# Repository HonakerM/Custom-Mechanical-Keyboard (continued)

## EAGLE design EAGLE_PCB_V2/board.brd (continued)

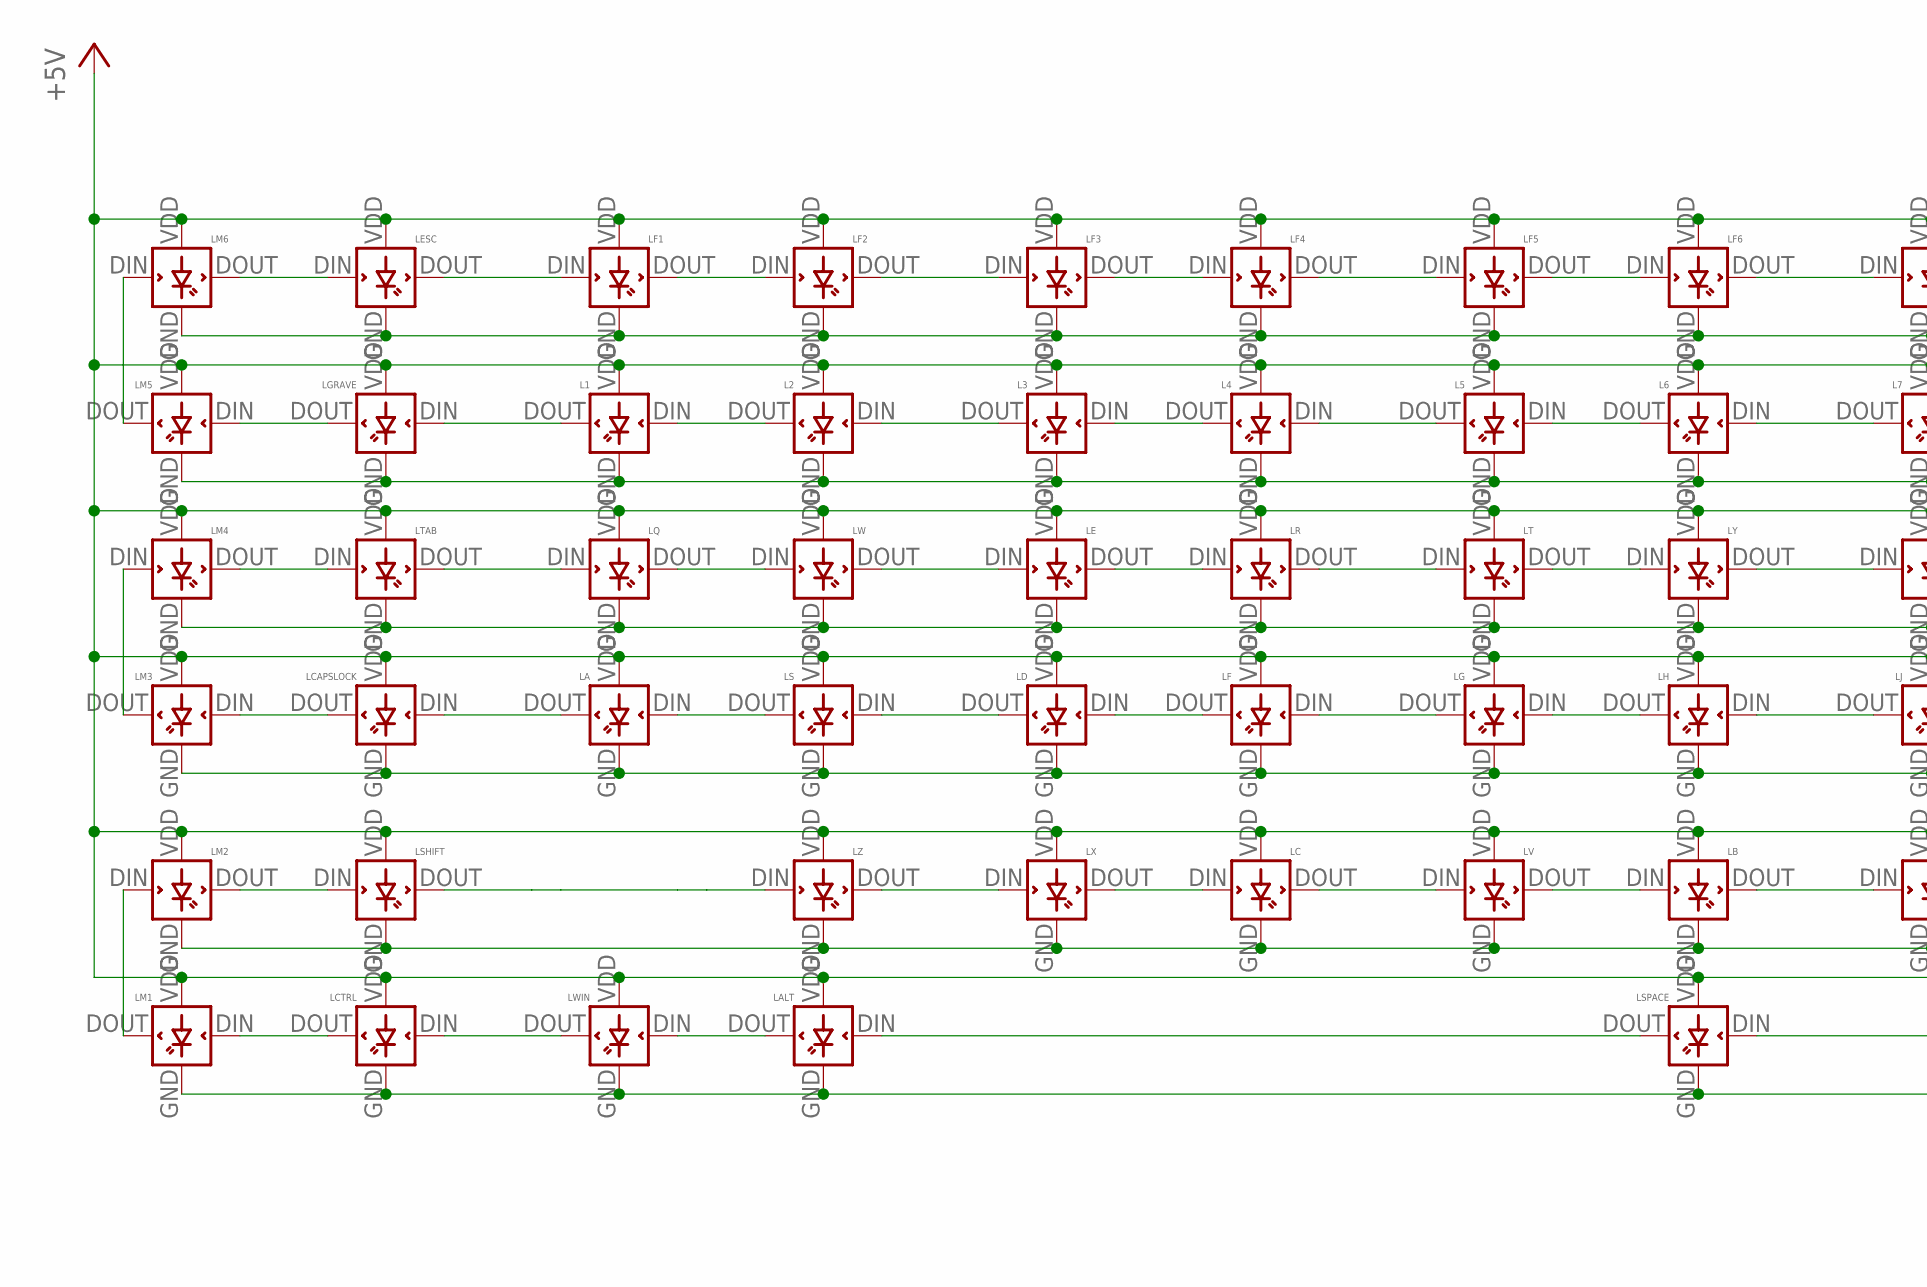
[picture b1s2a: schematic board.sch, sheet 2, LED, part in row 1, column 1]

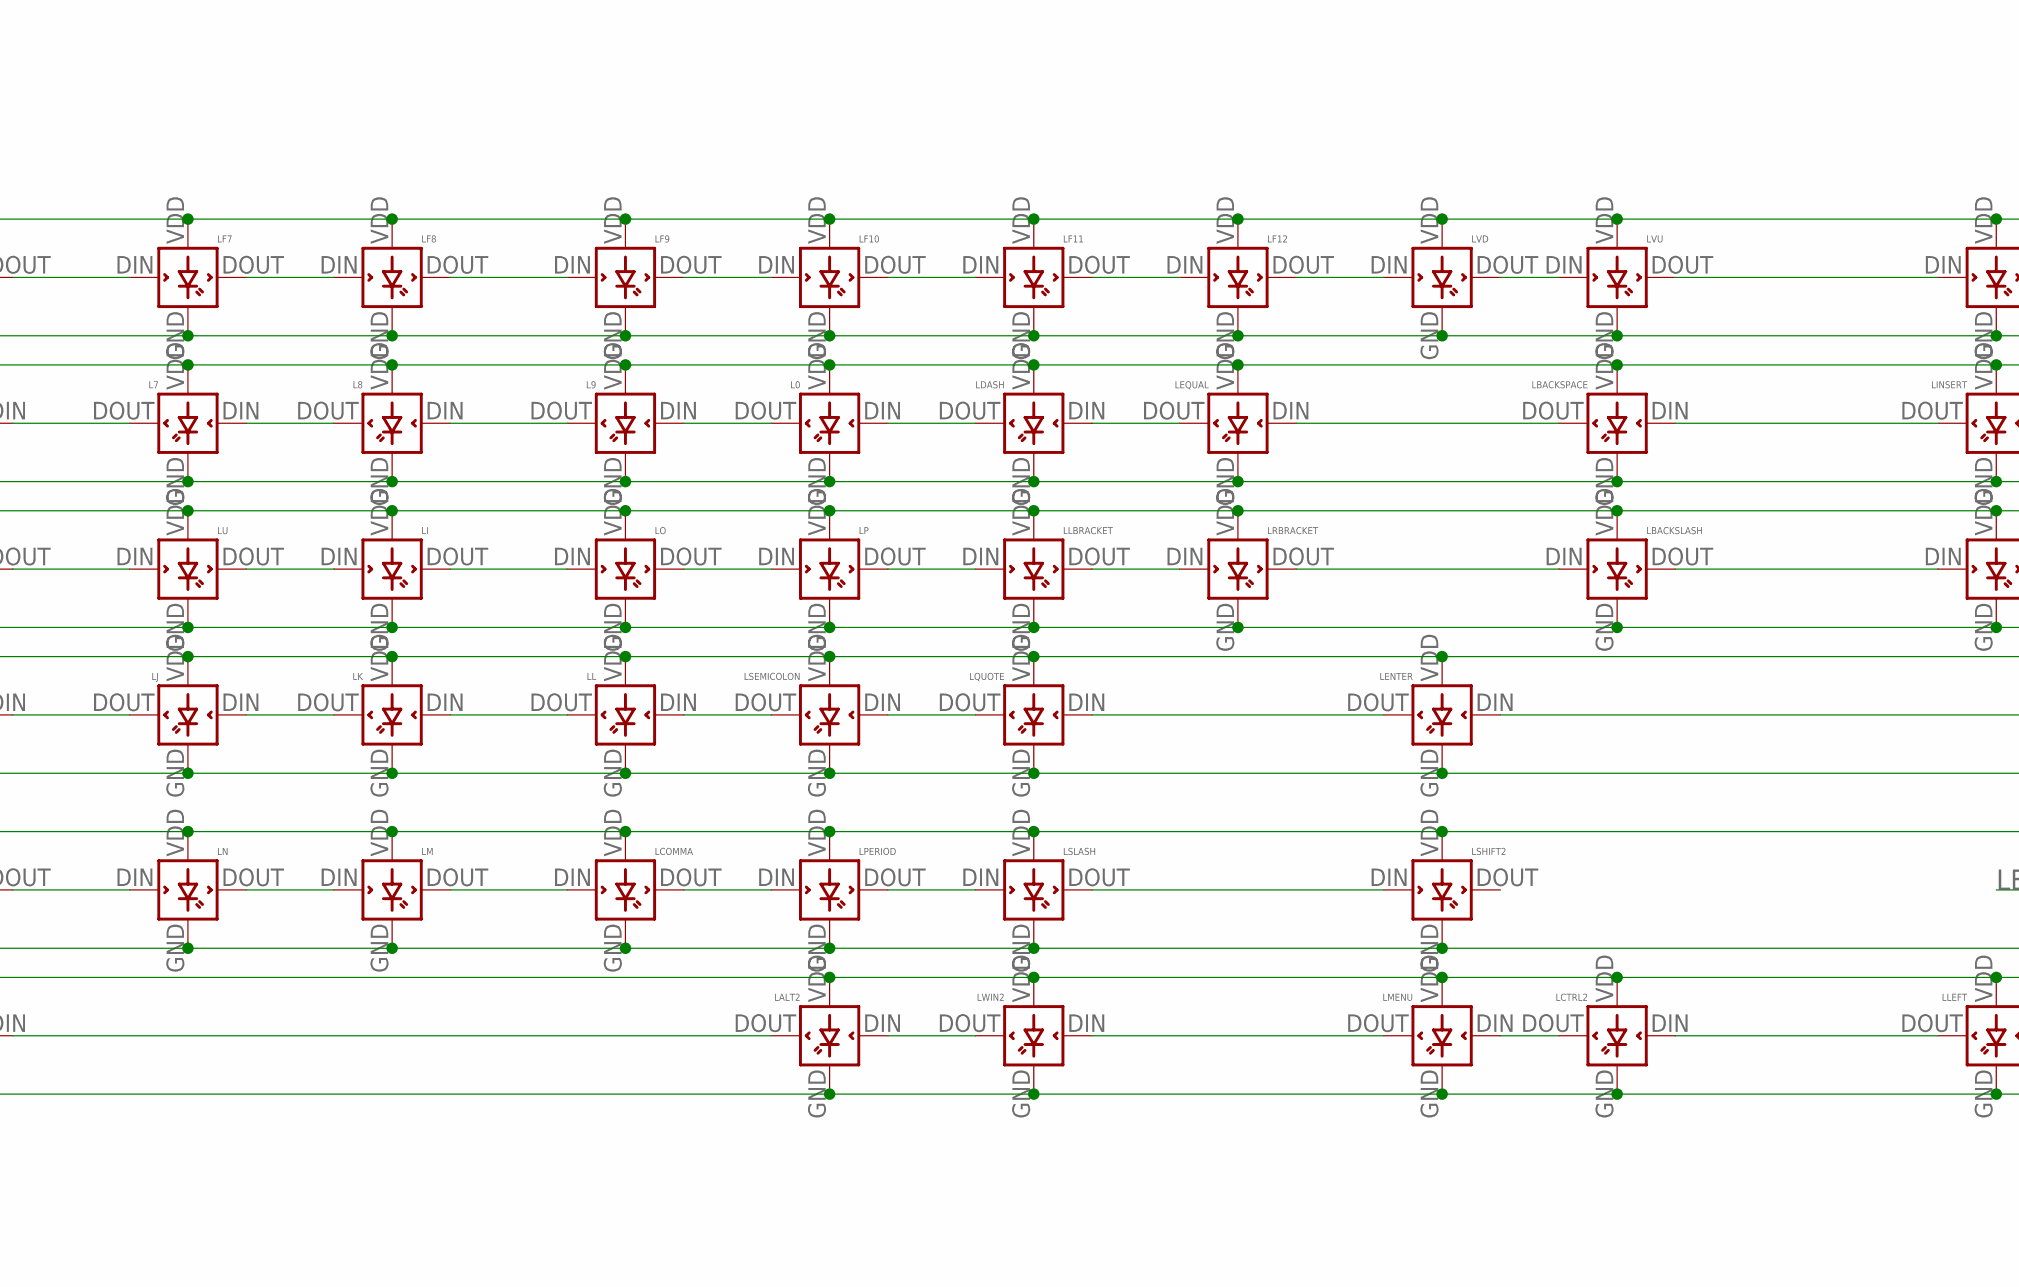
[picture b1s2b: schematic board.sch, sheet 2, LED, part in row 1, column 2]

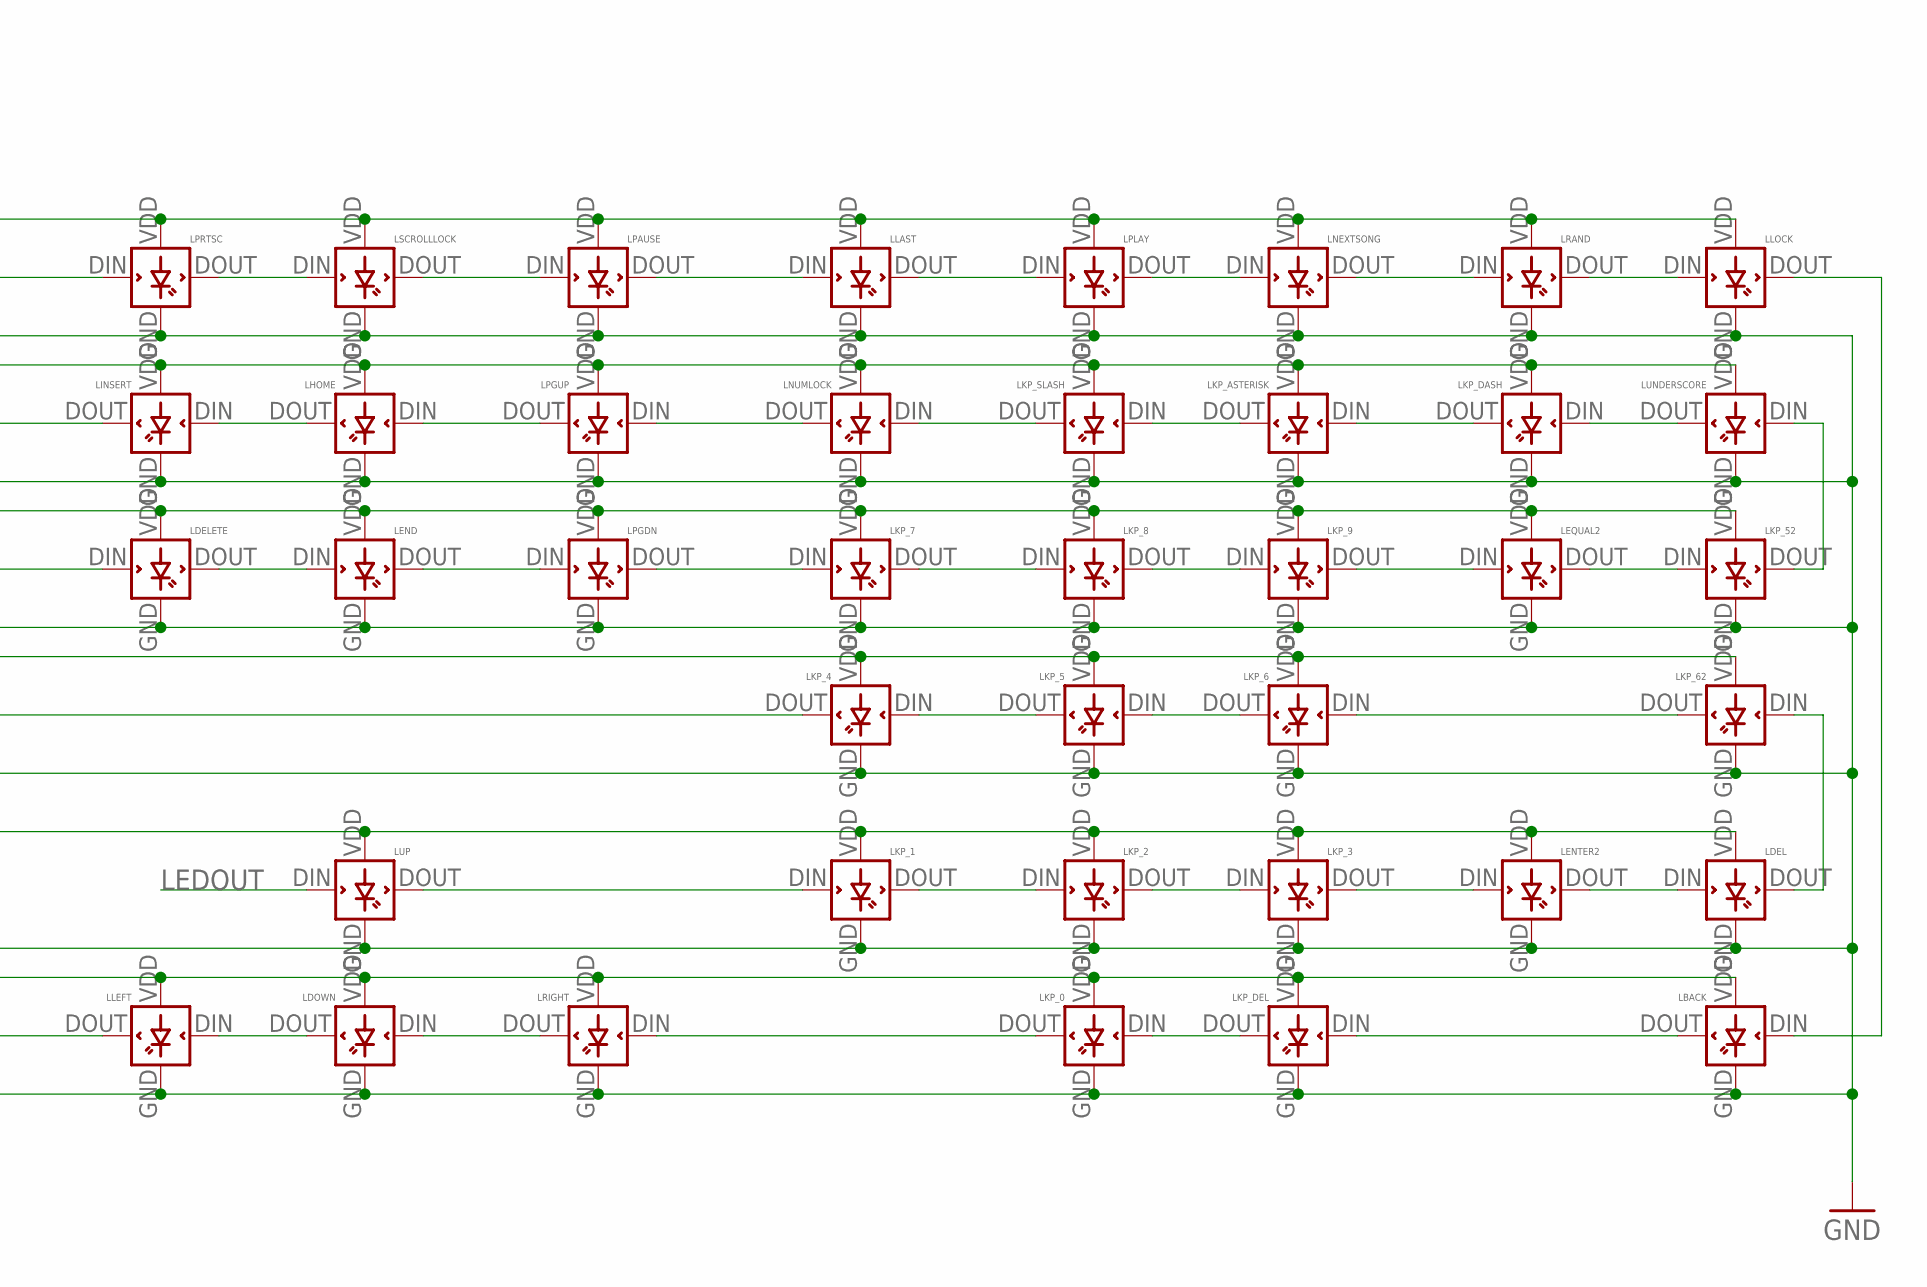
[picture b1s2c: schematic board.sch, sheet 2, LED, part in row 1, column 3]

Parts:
L0, L1, L2, L3, L4, L5, L6, L7, L8, L9: WS2812B-MINI
LA: WS2812B-MINI
LALT, LALT2: WS2812B-MINI
LB: WS2812B-MINI
LBACK: WS2812B-MINI
LBACKSLASH: WS2812B-MINI
LBACKSPACE: WS2812B-MINI
LC: WS2812B-MINI
LCAPSLOCK: WS2812B-MINI
LCOMMA: WS2812B-MINI
LCTRL, LCTRL2: WS2812B-MINI
LD: WS2812B-MINI
LDASH: WS2812B-MINI
LDEL: WS2812B-MINI
LDELETE: WS2812B-MINI
LDOWN: WS2812B-MINI
LE: WS2812B-MINI
LEND: WS2812B-MINI
LENTER, LENTER2: WS2812B-MINI
LEQUAL, LEQUAL2: WS2812B-MINI
LESC: WS2812B-MINI
LF, LF1, LF2, LF3, LF4, LF5, LF6, LF7, LF8, LF9, LF10, LF11, LF12: WS2812B-MINI
LG: WS2812B-MINI
LGRAVE: WS2812B-MINI
LH: WS2812B-MINI
LHOME: WS2812B-MINI
LI: WS2812B-MINI
LINSERT: WS2812B-MINI
LJ: WS2812B-MINI
LK: WS2812B-MINI
LKP_0, LKP_1, LKP_2, LKP_3, LKP_4, LKP_5, LKP_6, LKP_7, LKP_8, LKP_9, LKP_52, LKP_62: WS2812B-MINI
LKP_ASTERISK: WS2812B-MINI
LKP_DASH: WS2812B-MINI
LKP_DEL: WS2812B-MINI
LKP_SLASH: WS2812B-MINI
LL: WS2812B-MINI
LLAST: WS2812B-MINI
LLBRACKET: WS2812B-MINI
LLEFT: WS2812B-MINI
LLOCK: WS2812B-MINI
LM, LM1, LM2, LM3, LM4, LM5, LM6: WS2812B-MINI
LMENU: WS2812B-MINI
LN: WS2812B-MINI
LNEXTSONG: WS2812B-MINI
LNUMLOCK: WS2812B-MINI
LO: WS2812B-MINI
LP: WS2812B-MINI
LPAUSE: WS2812B-MINI
LPERIOD: WS2812B-MINI
LPGDN: WS2812B-MINI
LPGUP: WS2812B-MINI
LPLAY: WS2812B-MINI
LPRTSC: WS2812B-MINI
LQ: WS2812B-MINI
LQUOTE: WS2812B-MINI
LR: WS2812B-MINI
LRAND: WS2812B-MINI
LRBRACKET: WS2812B-MINI
LRIGHT: WS2812B-MINI
LS: WS2812B-MINI
LSCROLLLOCK: WS2812B-MINI
LSEMICOLON: WS2812B-MINI
LSHIFT, LSHIFT2: WS2812B-MINI
LSLASH: WS2812B-MINI
LSPACE: WS2812B-MINI
LT: WS2812B-MINI
LTAB: WS2812B-MINI
LU: WS2812B-MINI
LUNDERSCORE: WS2812B-MINI
LUP: WS2812B-MINI
LV: WS2812B-MINI
LVD: WS2812B-MINI
LVU: WS2812B-MINI
LW: WS2812B-MINI
LWIN, LWIN2: WS2812B-MINI
LX: WS2812B-MINI
LY: WS2812B-MINI
LZ: WS2812B-MINI

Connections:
+5V: L0.VDD, L1.VDD, L2.VDD, L3.VDD, L4.VDD, L5.VDD, L6.VDD, L7.VDD, L8.VDD, L9.VDD, LA.VDD, LALT.VDD, LALT2.VDD, LB.VDD, LBACK.VDD, LBACKSLASH.VDD, LBACKSPACE.VDD, LC.VDD, LCAPSLOCK.VDD, LCOMMA.VDD, LCTRL.VDD, LCTRL2.VDD, LD.VDD, LDASH.VDD, LDEL.VDD, LDELETE.VDD, LDOWN.VDD, LE.VDD, LEND.VDD, LENTER.VDD, LENTER2.VDD, LEQUAL.VDD, LEQUAL2.VDD, LESC.VDD, LF.VDD, LF1.VDD, LF2.VDD, LF3.VDD, LF4.VDD, LF5.VDD, LF6.VDD, LF7.VDD, LF8.VDD, LF9.VDD, LF10.VDD, LF11.VDD, LF12.VDD, LG.VDD, LGRAVE.VDD, LH.VDD, LHOME.VDD, LI.VDD, LINSERT.VDD, LJ.VDD, LK.VDD, LKP_0.VDD, LKP_1.VDD, LKP_2.VDD, LKP_3.VDD, LKP_4.VDD, LKP_5.VDD, LKP_6.VDD, LKP_7.VDD, LKP_8.VDD, LKP_9.VDD, LKP_52.VDD, LKP_62.VDD, LKP_ASTERISK.VDD, LKP_DASH.VDD, LKP_DEL.VDD, LKP_SLASH.VDD, LL.VDD, LLAST.VDD, LLBRACKET.VDD, LLEFT.VDD, LLOCK.VDD, LM.VDD, LM1.VDD, LM2.VDD, LM3.VDD, LM4.VDD, LM5.VDD, LM6.VDD, LMENU.VDD, LN.VDD, LNEXTSONG.VDD, LNUMLOCK.VDD, LO.VDD, LP.VDD, LPAUSE.VDD, LPERIOD.VDD, LPGDN.VDD, LPGUP.VDD, LPLAY.VDD, LPRTSC.VDD, LQ.VDD, LQUOTE.VDD, LR.VDD, LRAND.VDD, LRBRACKET.VDD, LRIGHT.VDD, LS.VDD, LSCROLLLOCK.VDD, LSEMICOLON.VDD, LSHIFT.VDD, LSHIFT2.VDD, LSLASH.VDD, LSPACE.VDD, LT.VDD, LTAB.VDD, LU.VDD, LUNDERSCORE.VDD, LUP.VDD, LV.VDD, LVD.VDD, LVU.VDD, LW.VDD, LWIN.VDD, LWIN2.VDD, LX.VDD, LY.VDD, LZ.VDD; also elsewhere on the board
GND: L0.GND, L1.GND, L2.GND, L3.GND, L4.GND, L5.GND, L6.GND, L7.GND, L8.GND, L9.GND, LA.GND, LALT.GND, LALT2.GND, LB.GND, LBACK.GND, LBACKSLASH.GND, LBACKSPACE.GND, LC.GND, LCAPSLOCK.GND, LCOMMA.GND, LCTRL.GND, LCTRL2.GND, LD.GND, LDASH.GND, LDEL.GND, LDELETE.GND, LDOWN.GND, LE.GND, LEND.GND, LENTER.GND, LENTER2.GND, LEQUAL.GND, LEQUAL2.GND, LESC.GND, LF.GND, LF1.GND, LF2.GND, LF3.GND, LF4.GND, LF5.GND, LF6.GND, LF7.GND, LF8.GND, LF9.GND, LF10.GND, LF11.GND, LF12.GND, LG.GND, LGRAVE.GND, LH.GND, LHOME.GND, LI.GND, LINSERT.GND, LJ.GND, LK.GND, LKP_0.GND, LKP_1.GND, LKP_2.GND, LKP_3.GND, LKP_4.GND, LKP_5.GND, LKP_6.GND, LKP_7.GND, LKP_8.GND, LKP_9.GND, LKP_52.GND, LKP_62.GND, LKP_ASTERISK.GND, LKP_DASH.GND, LKP_DEL.GND, LKP_SLASH.GND, LL.GND, LLAST.GND, LLBRACKET.GND, LLEFT.GND, LLOCK.GND, LM.GND, LM1.GND, LM2.GND, LM3.GND, LM4.GND, LM5.GND, LM6.GND, LMENU.GND, LN.GND, LNEXTSONG.GND, LNUMLOCK.GND, LO.GND, LP.GND, LPAUSE.GND, LPERIOD.GND, LPGDN.GND, LPGUP.GND, LPLAY.GND, LPRTSC.GND, LQ.GND, LQUOTE.GND, LR.GND, LRAND.GND, LRBRACKET.GND, LRIGHT.GND, LS.GND, LSCROLLLOCK.GND, LSEMICOLON.GND, LSHIFT.GND, LSHIFT2.GND, LSLASH.GND, LSPACE.GND, LT.GND, LTAB.GND, LU.GND, LUNDERSCORE.GND, LUP.GND, LV.GND, LVD.GND, LVU.GND, LW.GND, LWIN.GND, LWIN2.GND, LX.GND, LY.GND, LZ.GND; also elsewhere on the board
LEDOUT: LUP.DIN; also elsewhere on the board
unnamed: LESC.DIN, LM6.DOUT
unnamed: LESC.DOUT, LF1.DIN
unnamed: LF1.DOUT, LF2.DIN
unnamed: LF2.DOUT, LF3.DIN
unnamed: LF3.DOUT, LF4.DIN
unnamed: LF4.DOUT, LF5.DIN
unnamed: LF5.DOUT, LF6.DIN
unnamed: LF6.DOUT, LF7.DIN
unnamed: LF7.DOUT, LF8.DIN
unnamed: LF8.DOUT, LF9.DIN
unnamed: LF9.DOUT, LF10.DIN
unnamed: LF10.DOUT, LF11.DIN
unnamed: LF11.DOUT, LF12.DIN
unnamed: LF12.DOUT, LVD.DIN
unnamed: LVD.DOUT, LVU.DIN
unnamed: LPRTSC.DIN, LVU.DOUT
unnamed: LPRTSC.DOUT, LSCROLLLOCK.DIN
unnamed: LPAUSE.DIN, LSCROLLLOCK.DOUT
unnamed: LLAST.DIN, LPAUSE.DOUT
unnamed: LLAST.DOUT, LPLAY.DIN
unnamed: LNEXTSONG.DOUT, LRAND.DIN
unnamed: LNEXTSONG.DIN, LPLAY.DOUT
unnamed: LLOCK.DIN, LRAND.DOUT
unnamed: LGRAVE.DOUT, LM5.DIN
unnamed: L1.DOUT, LGRAVE.DIN
unnamed: L1.DIN, L2.DOUT
unnamed: L2.DIN, L3.DOUT
unnamed: L3.DIN, L4.DOUT
unnamed: L4.DIN, L5.DOUT
unnamed: L5.DIN, L6.DOUT
unnamed: L6.DIN, L7.DOUT
unnamed: L7.DIN, L8.DOUT
unnamed: L8.DIN, L9.DOUT
unnamed: L0.DOUT, L9.DIN
unnamed: L0.DIN, LDASH.DOUT
unnamed: LDASH.DIN, LEQUAL.DOUT
unnamed: LM4.DOUT, LTAB.DIN
unnamed: LBACKSPACE.DOUT, LEQUAL.DIN
unnamed: LCTRL.DOUT, LM1.DIN
unnamed: LBACKSPACE.DIN, LINSERT.DOUT
unnamed: LHOME.DOUT, LINSERT.DIN
unnamed: LHOME.DIN, LPGUP.DOUT
unnamed: LNUMLOCK.DOUT, LPGUP.DIN
unnamed: LKP_SLASH.DOUT, LNUMLOCK.DIN
unnamed: LKP_ASTERISK.DOUT, LKP_SLASH.DIN
unnamed: LKP_ASTERISK.DIN, LKP_DASH.DOUT
unnamed: LDEL.DOUT, LKP_62.DIN
unnamed: LQ.DIN, LTAB.DOUT
unnamed: LQ.DOUT, LW.DIN
unnamed: LE.DIN, LW.DOUT
unnamed: LE.DOUT, LR.DIN
unnamed: LR.DOUT, LT.DIN
unnamed: LT.DOUT, LY.DIN
unnamed: LU.DIN, LY.DOUT
unnamed: LI.DIN, LU.DOUT
unnamed: LI.DOUT, LO.DIN
unnamed: LO.DOUT, LP.DIN
unnamed: LLBRACKET.DIN, LP.DOUT
unnamed: LLBRACKET.DOUT, LRBRACKET.DIN
unnamed: LBACKSLASH.DIN, LRBRACKET.DOUT
unnamed: LM3.DOUT, LM4.DIN
unnamed: LBACKSLASH.DOUT, LDELETE.DIN
unnamed: LDELETE.DOUT, LEND.DIN
unnamed: LEND.DOUT, LPGDN.DIN
unnamed: LKP_7.DIN, LPGDN.DOUT
unnamed: LKP_7.DOUT, LKP_8.DIN
unnamed: LEQUAL2.DIN, LKP_9.DOUT
unnamed: LKP_8.DOUT, LKP_9.DIN
unnamed: LEQUAL2.DOUT, LKP_52.DIN
unnamed: LCAPSLOCK.DOUT, LM3.DIN
unnamed: LA.DOUT, LCAPSLOCK.DIN
unnamed: LA.DIN, LS.DOUT
unnamed: LD.DOUT, LS.DIN
unnamed: LD.DIN, LF.DOUT
unnamed: LF.DIN, LG.DOUT
unnamed: LG.DIN, LH.DOUT
unnamed: LH.DIN, LJ.DOUT
unnamed: LJ.DIN, LK.DOUT
unnamed: LK.DIN, LL.DOUT
unnamed: LL.DIN, LSEMICOLON.DOUT
unnamed: LQUOTE.DOUT, LSEMICOLON.DIN
unnamed: LM2.DOUT, LSHIFT.DIN
unnamed: LSHIFT.DOUT, LZ.DIN
unnamed: LCTRL.DIN, LWIN.DOUT
unnamed: LX.DIN, LZ.DOUT
unnamed: LC.DIN, LX.DOUT
unnamed: LENTER.DOUT, LQUOTE.DIN
unnamed: LENTER.DIN, LKP_4.DOUT
unnamed: LC.DOUT, LV.DIN
unnamed: LKP_4.DIN, LKP_5.DOUT
unnamed: LKP_5.DIN, LKP_6.DOUT
unnamed: LB.DIN, LV.DOUT
unnamed: LB.DOUT, LN.DIN
unnamed: LM.DIN, LN.DOUT
unnamed: LCOMMA.DIN, LM.DOUT
unnamed: LCOMMA.DOUT, LPERIOD.DIN
unnamed: LPERIOD.DOUT, LSLASH.DIN
unnamed: LALT.DOUT, LWIN.DIN
unnamed: LSHIFT2.DIN, LSLASH.DOUT
unnamed: LALT.DIN, LSPACE.DOUT
unnamed: LALT2.DOUT, LSPACE.DIN
unnamed: LKP_6.DIN, LKP_62.DOUT
unnamed: LKP_52.DOUT, LUNDERSCORE.DIN
unnamed: LKP_1.DIN, LUP.DOUT
unnamed: LKP_1.DOUT, LKP_2.DIN
unnamed: LENTER2.DIN, LKP_3.DOUT
unnamed: LKP_2.DOUT, LKP_3.DIN
unnamed: LDEL.DIN, LENTER2.DOUT
unnamed: LKP_DASH.DIN, LUNDERSCORE.DOUT
unnamed: LALT2.DIN, LWIN2.DOUT
unnamed: LM5.DOUT, LM6.DIN
unnamed: LBACK.DIN, LLOCK.DOUT
unnamed: LMENU.DOUT, LWIN2.DIN
unnamed: LCTRL2.DOUT, LMENU.DIN
unnamed: LCTRL2.DIN, LLEFT.DOUT
unnamed: LDOWN.DOUT, LLEFT.DIN
unnamed: LDOWN.DIN, LRIGHT.DOUT
unnamed: LKP_0.DOUT, LRIGHT.DIN
unnamed: LKP_0.DIN, LKP_DEL.DOUT
unnamed: LBACK.DOUT, LKP_DEL.DIN
unnamed: LM1.DOUT, LM2.DIN

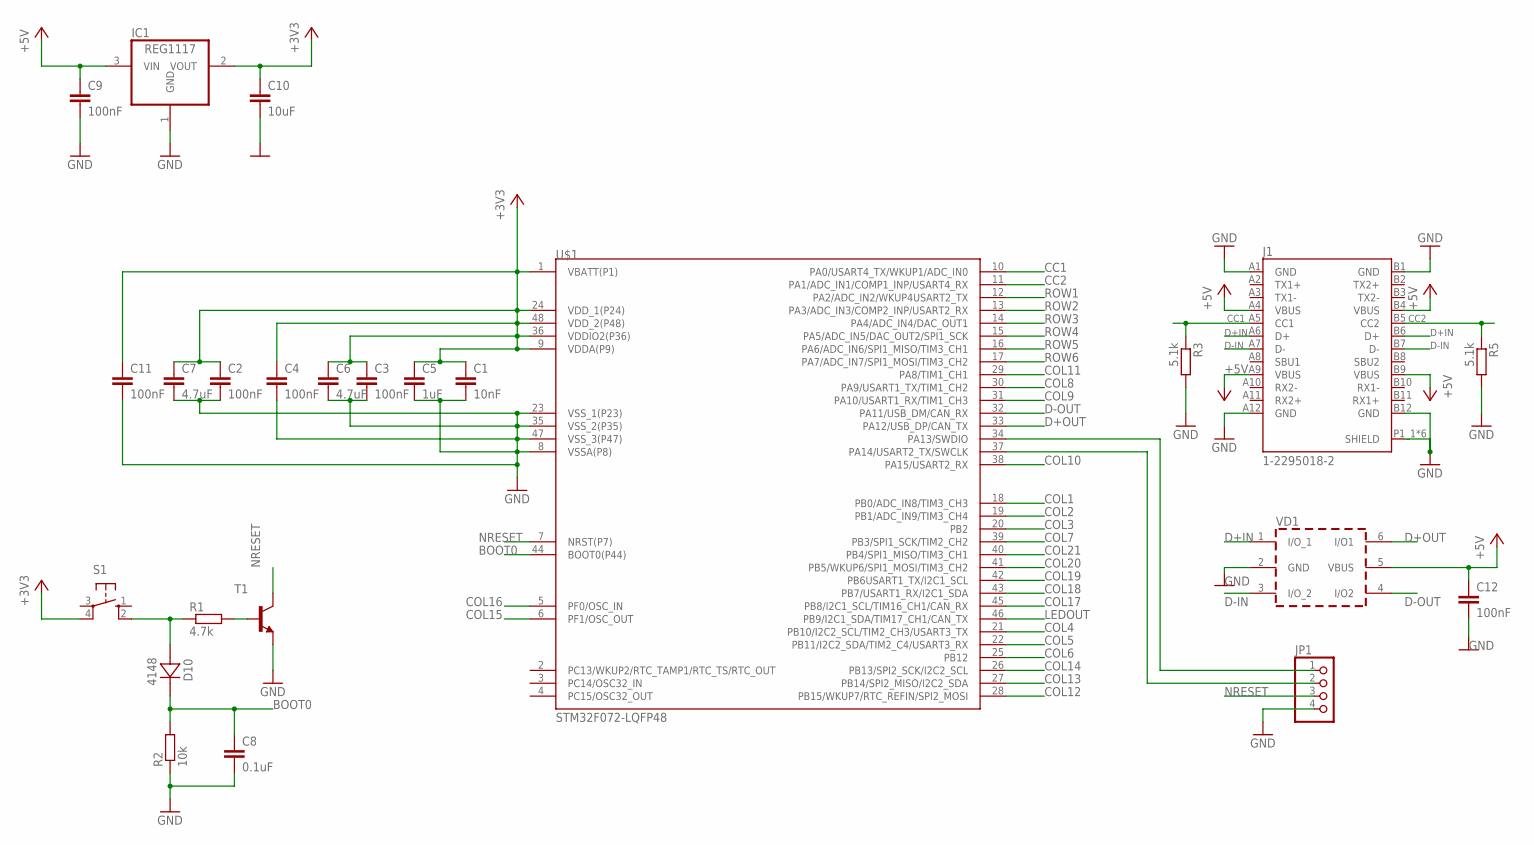
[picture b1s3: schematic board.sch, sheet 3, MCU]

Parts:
C1: 10nF; C0402
C2, C3, C4, C9, C11: 100nF; C0402
C5: 1uF; C0402
C6, C7: 4.7uF; C0402
C8: 0.1uF; C0402
C10: 10uF; C0402
C12: 100nF; C0805
D10: 4148; SOD-123
IC1: REG1117; SOT223
J1: 1-2295018-2; TE_1-2295018-2
JP1: PINHD-1X4; 1X04
R1: 4.7k; R0603
R2: 10k; R0603
R3, R5: 5.1k; R0603
S1: 10-XX; B3F-10XX
T1: -NPN-SOT23-EBC; SOT23-EBC
U$1: STM32F072-LQFP48; LQFP48
VD1: USBLC6-2SC6; SOT-23-6L

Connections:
+3V3: C1.1, C2.1, C3.1, C4.1, C5.1, C6.1, C7.1, C10.1, C11.1, IC1.2 (VOUT), S1.4 (P1), U$1.1 (VBATT(P1)), U$1.9 (VDDA(P9)), U$1.24 (VDD_1(P24)), U$1.36 (VDDIO2(P36)), U$1.48 (VDD_2(P48))
+5V: C9.1, C12.1, IC1.3 (VIN), J1.A4 (VBUS), J1.A9 (VBUS), J1.B4 (VBUS), J1.B9 (VBUS), VD1.5 (VBUS); also elsewhere on the board
BOOT0: C8.1, D10.C, R2.2, U$1.44 (BOOT0(P44))
CC1: J1.A5 (CC1), R3.1, U$1.10 (PA0/USART4_TX/WKUP1/ADC_IN0)
CC2: J1.B5 (CC2), R5.1, U$1.11 (PA1/ADC_IN1/COMP1_INP/USART4_RX)
COL1: U$1.18 (PB0/ADC_IN8/TIM3_CH3); also elsewhere on the board
COL2: U$1.19 (PB1/ADC_IN9/TIM3_CH4); also elsewhere on the board
COL3: U$1.20 (PB2); also elsewhere on the board
COL4: U$1.21 (PB10/I2C2_SCL/TIM2_CH3/USART3_TX); also elsewhere on the board
COL5: U$1.22 (PB11/I2C2_SDA/TIM2_C4/USART3_RX); also elsewhere on the board
COL6: U$1.25 (PB12); also elsewhere on the board
COL7: U$1.39 (PB3/SPI1_SCK/TIM2_CH2); also elsewhere on the board
COL8: U$1.30 (PA9/USART1_TX/TIM1_CH2); also elsewhere on the board
COL9: U$1.31 (PA10/USART1_RX/TIM1_CH3); also elsewhere on the board
COL10: U$1.38 (PA15/USART2_RX); also elsewhere on the board
COL11: U$1.29 (PA8/TIM1_CH1); also elsewhere on the board
COL12: U$1.28 (PB15/WKUP7/RTC_REFIN/SPI2_MOSI); also elsewhere on the board
COL13: U$1.27 (PB14/SPI2_MISO/I2C2_SDA); also elsewhere on the board
COL14: U$1.26 (PB13/SPI2_SCK/I2C2_SCL); also elsewhere on the board
COL15: U$1.6 (PF1/OSC_OUT); also elsewhere on the board
COL16: U$1.5 (PF0/OSC_IN); also elsewhere on the board
COL17: U$1.45 (PB8/I2C1_SCL/TIM16_CH1/CAN_RX); also elsewhere on the board
COL18: U$1.43 (PB7/USART1_RX/I2C1_SDA); also elsewhere on the board
COL19: U$1.42 (PB6USART1_TX/I2C1_SCL); also elsewhere on the board
COL20: U$1.41 (PB5/WKUP6/SPI1_MOSI/TIM3_CH2); also elsewhere on the board
COL21: U$1.40 (PB4/SPI1_MISO/TIM3_CH1); also elsewhere on the board
D+IN: J1.A6 (D+), J1.B6 (D+), VD1.1 (I/O_1)
D+OUT: U$1.33 (PA12/USB_DP/CAN_TX), VD1.6 (I/O1)
D-IN: J1.A7 (D-), J1.B7 (D-), VD1.3 (I/O_2)
D-OUT: U$1.32 (PA11/USB_DM/CAN_RX), VD1.4 (I/O2)
GND: C1.2, C2.2, C3.2, C4.2, C5.2, C6.2, C7.2, C8.2, C9.2, C10.2, C11.2, C12.2, IC1.1 (GND), J1.A1 (GND), J1.A12 (GND), J1.B1 (GND), J1.B12 (GND), J1.P1_1 (SHIELD), J1.P1_2 (SHIELD), J1.P2_1 (SHIELD), J1.P2_2 (SHIELD), J1.P4 (SHIELD), J1.P5 (SHIELD), JP1.4, R2.1, R3.2, R5.2, T1.E, U$1.8 (VSSA(P8)), U$1.23 (VSS_1(P23)), U$1.35 (VSS_2(P35)), U$1.47 (VSS_3(P47)), VD1.2 (GND); also elsewhere on the board
LEDOUT: U$1.46 (PB9/I2C1_SDA/TIM17_CH1/CAN_TX); also elsewhere on the board
unnamed: JP1.1, U$1.34 (PA13/SWDIO)
unnamed: JP1.2, U$1.37 (PA14/USART2_TX/SWCLK)
unnamed: D10.A, R1.1, S1.2 (S1)
unnamed: R1.2, T1.B
NRESET: JP1.3, T1.C, U$1.7 (NRST(P7))
ROW1: U$1.12 (PA2/ADC_IN2/WKUP4USART2_TX); also elsewhere on the board
ROW2: U$1.13 (PA3/ADC_IN3/COMP2_INP/USART2_RX); also elsewhere on the board
ROW3: U$1.14 (PA4/ADC_IN4/DAC_OUT1); also elsewhere on the board
ROW4: U$1.15 (PA5/ADC_IN5/DAC_OUT2/SPI1_SCK); also elsewhere on the board
ROW5: U$1.16 (PA6/ADC_IN6/SPI1_MISO/TIM3_CH1); also elsewhere on the board
ROW6: U$1.17 (PA7/ADC_IN7/SPI1_MOSI/TIM3_CH2); also elsewhere on the board

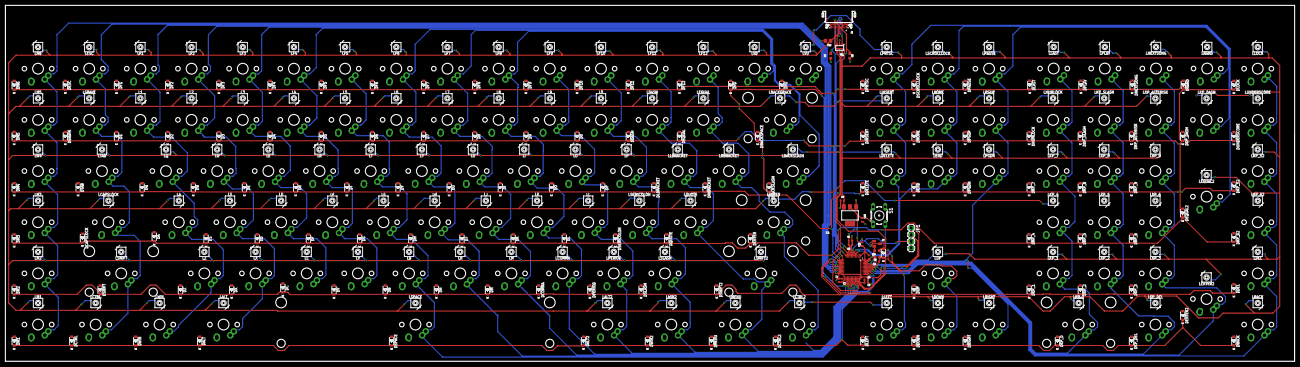
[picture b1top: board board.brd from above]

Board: 2 copper layers, 479.9 x 132.5 mm, 390 parts (0 on the bottom side), 164 nets.
